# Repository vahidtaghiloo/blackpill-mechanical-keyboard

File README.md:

# blackpill-mechanical-keyboard
stm32f411ceu6 black pill 44 key mechanical keyboard, inspired by Keyboardio Atreus (keyboardio.io)

The project is complete, the PCBs are manufactured and tested. The binary firmware
is [here](https://github.com/vahidtaghiloo/qmk-firmware-build/releases/tag/test)
and the qmk modified firmware is [here](https://github.com/vahidtaghiloo/qmk_firmware/tree/master/keyboards/blackpill_mechanical_keyboard)

# A few words:
- Due to current limitation of the onboard voltage regulator, some backlight 
  animations are not smooth. Changing the regulator is not an option because I
  could not find a similar package.
- Due to the higher frequency crystal (25 MHz), sometimes the black pill does not
  enter the DFU mode. Using a 12 Mhz oscilator seems to solve the issue.

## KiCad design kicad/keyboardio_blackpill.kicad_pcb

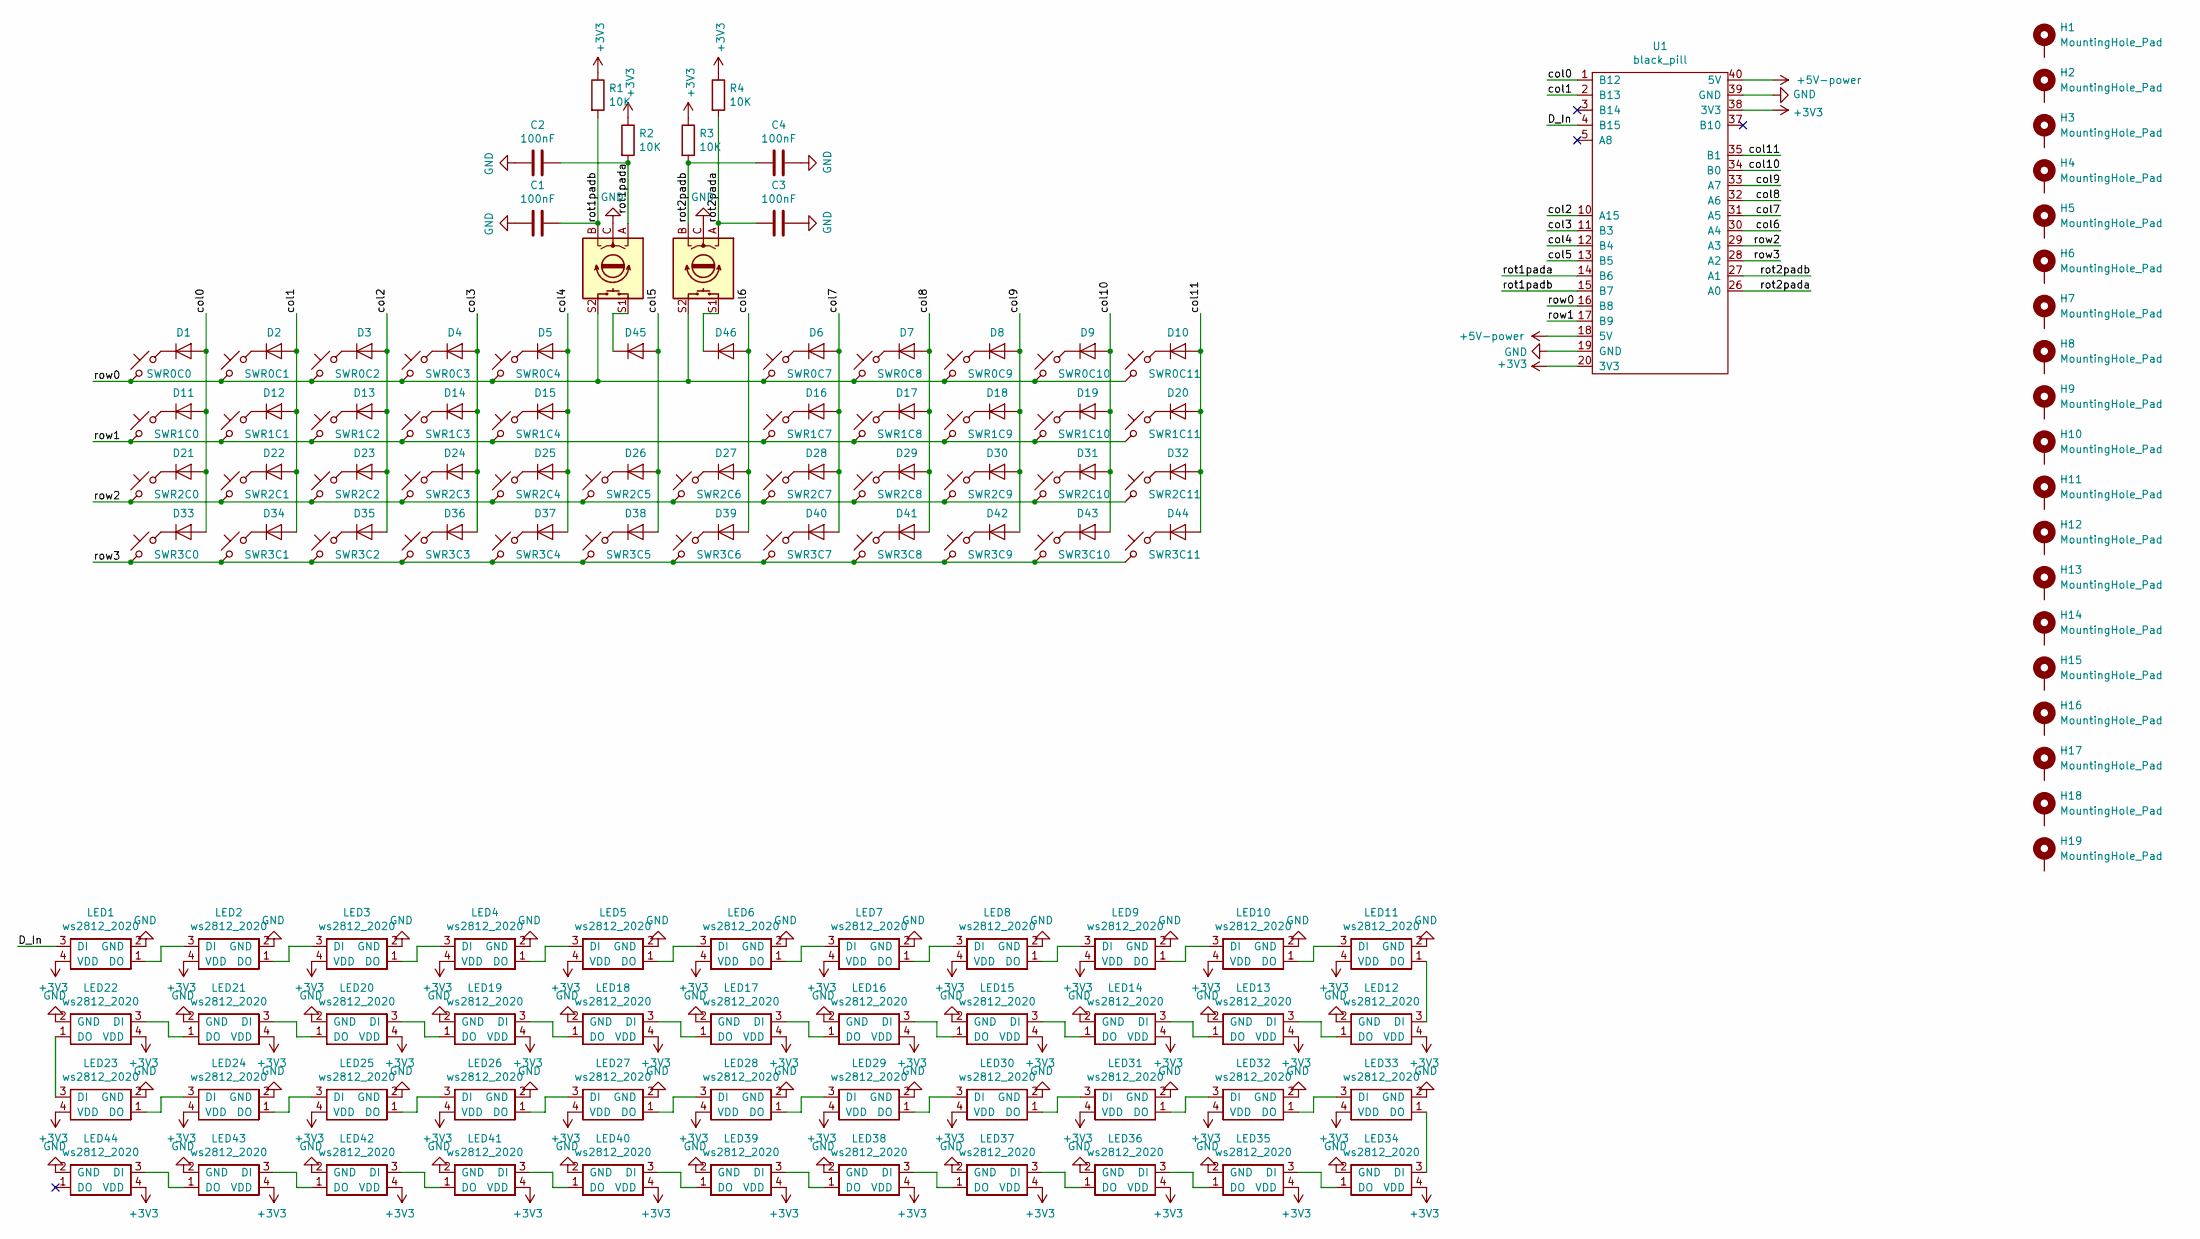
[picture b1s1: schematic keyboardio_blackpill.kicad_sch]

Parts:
C1, C2, C3, C4: 100nF; C_0805_2012Metric_Pad1.15x1.40mm_HandSolder
D1, D2, D3, D4, D5, D6, D7, D8, D9, D10, D11, D12, D13, D14, D15, D16, D17, D18, D19, D20, D21, D22, D23, D24, D25, D26, D27, D28, D29, D30, D31, D32, D33, D34, D35, D36, D37, D38, D39, D40, D41, D42, D43, D44, D45, D46: 1N4148; D_1206_3216Metric_Pad1.42x1.75mm_HandSolder
H1, H2, H3, H4, H5, H6, H7, H8, H9, H10, H11, H12, H13, H14, H15, H16, H17, H18, H19: MountingHole_Pad; MountingHole_2mm
LED1, LED2, LED3, LED4, LED5, LED6, LED7, LED8, LED9, LED10, LED11, LED12, LED13, LED14, LED15, LED16, LED17, LED18, LED19, LED20, LED21, LED22, LED23, LED24, LED25, LED26, LED27, LED28, LED29, LED30, LED31, LED32, LED33, LED34, LED35, LED36, LED37, LED38, LED39, LED40, LED41, LED42, LED43, LED44: ws2812_2020
R1, R2, R3, R4: 10K; R_0805_2012Metric_Pad1.15x1.40mm_HandSolder
SW1, SW2: Rotary_Encoder_Switch; RotaryEncoder_Alps_EC12E-Switch_Vertical_H20mm_CircularMoun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
SWR0C0, SWR0C1, SWR0C2, SWR0C3, SWR0C4, SWR0C7, SWR0C8, SWR0C9, SWR0C10, SWR0C11, SWR1C0, SWR1C1, SWR1C2, SWR1C3, SWR1C4, SWR1C7, SWR1C8, SWR1C9, SWR1C10, SWR1C11, SWR2C0, SWR2C1, SWR2C2, SWR2C3, SWR2C4, SWR2C5, SWR2C6, SWR2C7, SWR2C8, SWR2C9, SWR2C10, SWR2C11, SWR3C0, SWR3C1, SWR3C2, SWR3C3, SWR3C4, SWR3C5, SWR3C6, SWR3C7, SWR3C8, SWR3C9, SWR3C10, SWR3C11: SW_Push_45deg; cherryMX
U1: black_pill; stm32_blackpill

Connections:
+3V3: LED1.4 (VDD), LED2.4 (VDD), LED3.4 (VDD), LED4.4 (VDD), LED5.4 (VDD), LED6.4 (VDD), LED7.4 (VDD), LED8.4 (VDD), LED9.4 (VDD), LED10.4 (VDD), LED11.4 (VDD), LED12.4 (VDD), LED13.4 (VDD), LED14.4 (VDD), LED15.4 (VDD), LED16.4 (VDD), LED17.4 (VDD), LED18.4 (VDD), LED19.4 (VDD), LED20.4 (VDD), LED21.4 (VDD), LED22.4 (VDD), LED23.4 (VDD), LED24.4 (VDD), LED25.4 (VDD), LED26.4 (VDD), LED27.4 (VDD), LED28.4 (VDD), LED29.4 (VDD), LED30.4 (VDD), LED31.4 (VDD), LED32.4 (VDD), LED33.4 (VDD), LED34.4 (VDD), LED35.4 (VDD), LED36.4 (VDD), LED37.4 (VDD), LED38.4 (VDD), LED39.4 (VDD), LED40.4 (VDD), LED41.4 (VDD), LED42.4 (VDD), LED43.4 (VDD), LED44.4 (VDD), R1.1, R2.1, R3.1, R4.1, U1.20 (3V3), U1.38 (3V3)
+5V: U1.18 (5V), U1.40 (5V)
/D_In: LED1.3 (DI), U1.4 (B15)
/col0: D1.2 (A), D11.2 (A), D21.2 (A), D33.2 (A), U1.1 (B12)
/col1: D2.2 (A), D12.2 (A), D22.2 (A), D34.2 (A), U1.2 (B13)
/col2: D3.2 (A), D13.2 (A), D23.2 (A), D35.2 (A), U1.10 (A15)
/col3: D4.2 (A), D14.2 (A), D24.2 (A), D36.2 (A), U1.11 (B3)
/col4: D5.2 (A), D15.2 (A), D25.2 (A), D37.2 (A), U1.12 (B4)
/col5: D26.2 (A), D38.2 (A), D45.2 (A), U1.13 (B5)
/col6: D27.2 (A), D39.2 (A), D46.2 (A), U1.30 (A4)
/col7: D6.2 (A), D16.2 (A), D28.2 (A), D40.2 (A), U1.31 (A5)
/col8: D7.2 (A), D17.2 (A), D29.2 (A), D41.2 (A), U1.32 (A6)
/col9: D8.2 (A), D18.2 (A), D30.2 (A), D42.2 (A), U1.33 (A7)
/col10: D9.2 (A), D19.2 (A), D31.2 (A), D43.2 (A), U1.34 (B0)
/col11: D10.2 (A), D20.2 (A), D32.2 (A), D44.2 (A), U1.35 (B1)
/rot1pada: C2.1, R2.2, SW2.A, U1.14 (B6)
/rot1padb: C1.1, R1.2, SW2.B, U1.15 (B7)
/rot2pada: C3.2, R4.2, SW1.A, U1.26 (A0)
/rot2padb: C4.2, R3.2, SW1.B, U1.27 (A1)
/row0: SW1.S2, SW2.S2, SWR0C0.1, SWR0C1.1, SWR0C2.1, SWR0C3.1, SWR0C4.1, SWR0C7.1, SWR0C8.1, SWR0C9.1, SWR0C10.1, SWR0C11.1, U1.16 (B8)
/row1: SWR1C0.1, SWR1C1.1, SWR1C2.1, SWR1C3.1, SWR1C4.1, SWR1C7.1, SWR1C8.1, SWR1C9.1, SWR1C10.1, SWR1C11.1, U1.17 (B9)
/row2: SWR2C0.1, SWR2C1.1, SWR2C2.1, SWR2C3.1, SWR2C4.1, SWR2C5.1, SWR2C6.1, SWR2C7.1, SWR2C8.1, SWR2C9.1, SWR2C10.1, SWR2C11.1, U1.29 (A3)
/row3: SWR3C0.1, SWR3C1.1, SWR3C2.1, SWR3C3.1, SWR3C4.1, SWR3C5.1, SWR3C6.1, SWR3C7.1, SWR3C8.1, SWR3C9.1, SWR3C10.1, SWR3C11.1, U1.28 (A2)
GND: C1.2, C2.2, C3.1, C4.1, LED1.2 (GND), LED2.2 (GND), LED3.2 (GND), LED4.2 (GND), LED5.2 (GND), LED6.2 (GND), LED7.2 (GND), LED8.2 (GND), LED9.2 (GND), LED10.2 (GND), LED11.2 (GND), LED12.2 (GND), LED13.2 (GND), LED14.2 (GND), LED15.2 (GND), LED16.2 (GND), LED17.2 (GND), LED18.2 (GND), LED19.2 (GND), LED20.2 (GND), LED21.2 (GND), LED22.2 (GND), LED23.2 (GND), LED24.2 (GND), LED25.2 (GND), LED26.2 (GND), LED27.2 (GND), LED28.2 (GND), LED29.2 (GND), LED30.2 (GND), LED31.2 (GND), LED32.2 (GND), LED33.2 (GND), LED34.2 (GND), LED35.2 (GND), LED36.2 (GND), LED37.2 (GND), LED38.2 (GND), LED39.2 (GND), LED40.2 (GND), LED41.2 (GND), LED42.2 (GND), LED43.2 (GND), LED44.2 (GND), SW1.C, SW2.C, U1.19 (GND), U1.39 (GND)
unnamed: D1.1 (K), SWR0C0.2
unnamed: D2.1 (K), SWR0C1.2
unnamed: D3.1 (K), SWR0C2.2
unnamed: D4.1 (K), SWR0C3.2
unnamed: D5.1 (K), SWR0C4.2
unnamed: D6.1 (K), SWR0C7.2
unnamed: D7.1 (K), SWR0C8.2
unnamed: D8.1 (K), SWR0C9.2
unnamed: D9.1 (K), SWR0C10.2
unnamed: D10.1 (K), SWR0C11.2
unnamed: D11.1 (K), SWR1C0.2
unnamed: D12.1 (K), SWR1C1.2
unnamed: D13.1 (K), SWR1C2.2
unnamed: D14.1 (K), SWR1C3.2
unnamed: D15.1 (K), SWR1C4.2
unnamed: D16.1 (K), SWR1C7.2
unnamed: D17.1 (K), SWR1C8.2
unnamed: D18.1 (K), SWR1C9.2
unnamed: D19.1 (K), SWR1C10.2
unnamed: D20.1 (K), SWR1C11.2
unnamed: D21.1 (K), SWR2C0.2
unnamed: D22.1 (K), SWR2C1.2
unnamed: D23.1 (K), SWR2C2.2
unnamed: D24.1 (K), SWR2C3.2
unnamed: D25.1 (K), SWR2C4.2
unnamed: D26.1 (K), SWR2C5.2
unnamed: D27.1 (K), SWR2C6.2
unnamed: D28.1 (K), SWR2C7.2
unnamed: D29.1 (K), SWR2C8.2
unnamed: D30.1 (K), SWR2C9.2
unnamed: D31.1 (K), SWR2C10.2
unnamed: D32.1 (K), SWR2C11.2
unnamed: D33.1 (K), SWR3C0.2
unnamed: D34.1 (K), SWR3C1.2
unnamed: D35.1 (K), SWR3C2.2
unnamed: D36.1 (K), SWR3C3.2
unnamed: D37.1 (K), SWR3C4.2
unnamed: D38.1 (K), SWR3C5.2
unnamed: D39.1 (K), SWR3C6.2
unnamed: D40.1 (K), SWR3C7.2
unnamed: D41.1 (K), SWR3C8.2
unnamed: D42.1 (K), SWR3C9.2
unnamed: D43.1 (K), SWR3C10.2
unnamed: D44.1 (K), SWR3C11.2
unnamed: D45.1 (K), SW2.S1
unnamed: D46.1 (K), SW1.S1
unnamed: LED1.1 (DO), LED2.3 (DI)
unnamed: LED2.1 (DO), LED3.3 (DI)
unnamed: LED3.1 (DO), LED4.3 (DI)
unnamed: LED4.1 (DO), LED5.3 (DI)
unnamed: LED5.1 (DO), LED6.3 (DI)
unnamed: LED6.1 (DO), LED7.3 (DI)
unnamed: LED7.1 (DO), LED8.3 (DI)
unnamed: LED8.1 (DO), LED9.3 (DI)
unnamed: LED10.1 (DO), LED11.3 (DI)
unnamed: LED9.1 (DO), LED10.3 (DI)
unnamed: LED11.1 (DO), LED12.3 (DI)
unnamed: LED12.1 (DO), LED13.3 (DI)
unnamed: LED13.1 (DO), LED14.3 (DI)
unnamed: LED14.1 (DO), LED15.3 (DI)
unnamed: LED15.1 (DO), LED16.3 (DI)
unnamed: LED16.1 (DO), LED17.3 (DI)
unnamed: LED17.1 (DO), LED18.3 (DI)
unnamed: LED18.1 (DO), LED19.3 (DI)
unnamed: LED19.1 (DO), LED20.3 (DI)
unnamed: LED20.1 (DO), LED21.3 (DI)
unnamed: LED21.1 (DO), LED22.3 (DI)
unnamed: LED22.1 (DO), LED23.3 (DI)
unnamed: LED23.1 (DO), LED24.3 (DI)
unnamed: LED24.1 (DO), LED25.3 (DI)
unnamed: LED25.1 (DO), LED26.3 (DI)
unnamed: LED26.1 (DO), LED27.3 (DI)
unnamed: LED27.1 (DO), LED28.3 (DI)
unnamed: LED28.1 (DO), LED29.3 (DI)
unnamed: LED29.1 (DO), LED30.3 (DI)
unnamed: LED30.1 (DO), LED31.3 (DI)
unnamed: LED31.1 (DO), LED32.3 (DI)
unnamed: LED32.1 (DO), LED33.3 (DI)
unnamed: LED33.1 (DO), LED34.3 (DI)
unnamed: LED34.1 (DO), LED35.3 (DI)
unnamed: LED35.1 (DO), LED36.3 (DI)
unnamed: LED36.1 (DO), LED37.3 (DI)
unnamed: LED37.1 (DO), LED38.3 (DI)
unnamed: LED38.1 (DO), LED39.3 (DI)
unnamed: LED39.1 (DO), LED40.3 (DI)
unnamed: LED40.1 (DO), LED41.3 (DI)
unnamed: LED41.1 (DO), LED42.3 (DI)
unnamed: LED42.1 (DO), LED43.3 (DI)
unnamed: LED43.1 (DO), LED44.3 (DI)

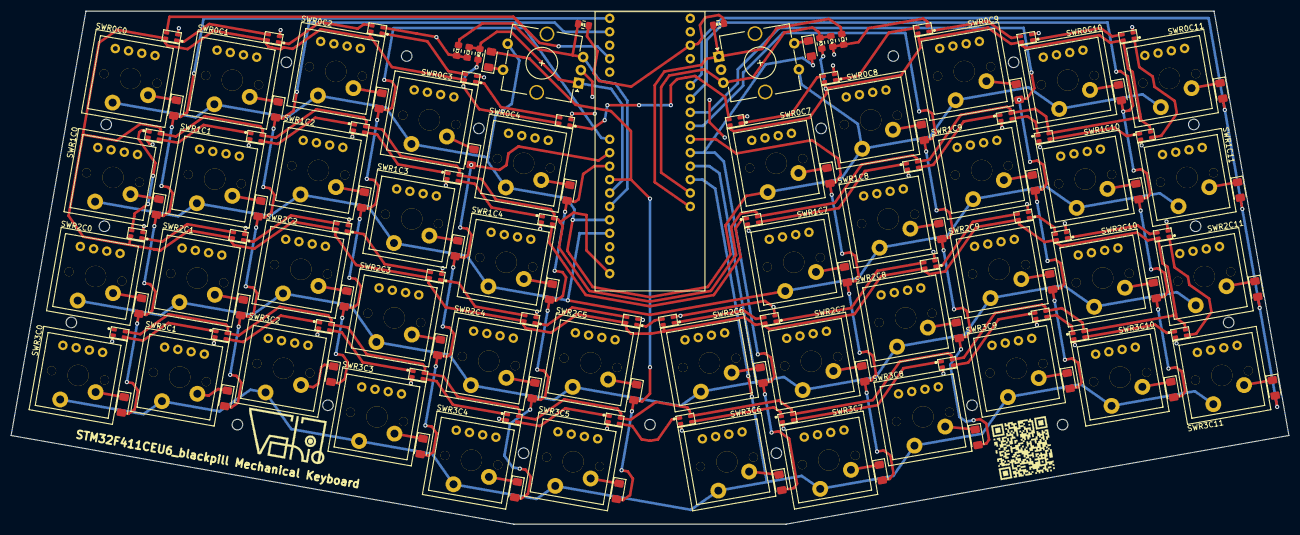
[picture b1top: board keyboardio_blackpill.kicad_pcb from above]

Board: 2 copper layers, 241.6 x 97.0 mm, 164 parts (0 on the bottom side), 113 nets.

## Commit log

2023-01-28 feat: Add Blackpill_keyboard Kicad Files
2023-01-28 chore: Update README.md
2023-01-29 chore: Add Keyboard PCB and Video
